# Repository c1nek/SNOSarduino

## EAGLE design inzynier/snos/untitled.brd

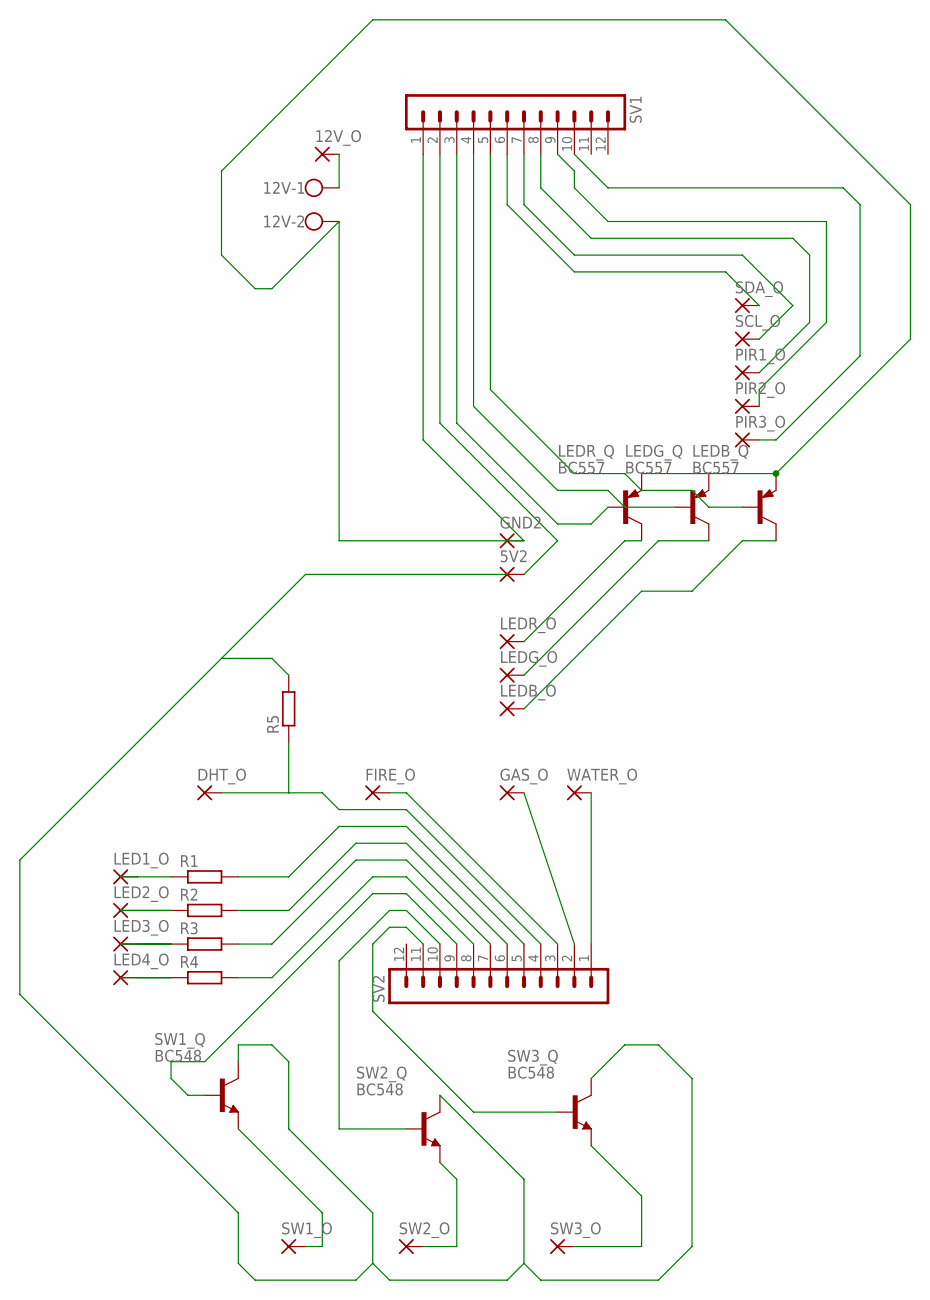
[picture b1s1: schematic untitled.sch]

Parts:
5V2, 12V_O: 1,6/0,8
12V: W237-102
DHT_O: 1,6/0,8
FIRE_O: 1,6/0,8
GAS_O: 1,6/0,8
GND2: 1,6/0,8
LED1_O, LED2_O, LED3_O, LED4_O: 1,6/0,8
LEDB_O: 1,6/0,8
LEDB_Q: BC557; TO92-EBC
LEDG_O: 1,6/0,8
LEDG_Q: BC557; TO92-EBC
LEDR_O: 1,6/0,8
LEDR_Q: BC557; TO92-EBC
PIR1_O, PIR2_O, PIR3_O: 1,6/0,8
R1, R2, R3, R4, R5: R-EU_0207/15; 0207/15
SCL_O: 1,6/0,8
SDA_O: 1,6/0,8
SV1, SV2: MA12-1W
SW1_O, SW2_O, SW3_O: 1,6/0,8
SW1_Q, SW2_Q, SW3_Q: BC548; TO92-EBC
WATER_O: 1,6/0,8

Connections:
unnamed: 12V.2, GND2.1, LEDB_Q.E, LEDG_Q.E, LEDR_Q.E, SV1.1
unnamed: 5V2.1, SV1.2
unnamed: LEDR_Q.B, SV1.3
unnamed: LEDG_Q.B, SV1.4
unnamed: LEDB_Q.B, SV1.5
unnamed: SDA_O.1, SV1.6
unnamed: SCL_O.1, SV1.7
unnamed: PIR1_O.1, SV1.8
unnamed: PIR2_O.1, SV1.9
unnamed: PIR3_O.1, SV1.10
unnamed: SV2.1, WATER_O.1
unnamed: GAS_O.1, SV2.2
unnamed: FIRE_O.1, SV2.3
unnamed: DHT_O.1, R5.1, SV2.4
unnamed: SV2.11, SW3_Q.B
unnamed: SV2.10, SW2_Q.B
unnamed: SV2.9, SW1_Q.B
unnamed: R4.2, SV2.8
unnamed: R3.2, SV2.7
unnamed: R2.2, SV2.6
unnamed: R1.2, SV2.5
unnamed: LED4_O.1, R4.1
unnamed: LED3_O.1, R3.1
unnamed: LED2_O.1, R2.1
unnamed: LED1_O.1, R1.1
unnamed: LEDR_O.1, LEDR_Q.C
unnamed: LEDG_O.1, LEDG_Q.C
unnamed: R5.2, SW1_Q.C, SW2_Q.C, SW3_Q.C
unnamed: LEDB_O.1, LEDB_Q.C
unnamed: SW1_O.1, SW1_Q.E
unnamed: SW2_O.1, SW2_Q.E
unnamed: SW3_O.1, SW3_Q.E
unnamed: 12V.1, 12V_O.1

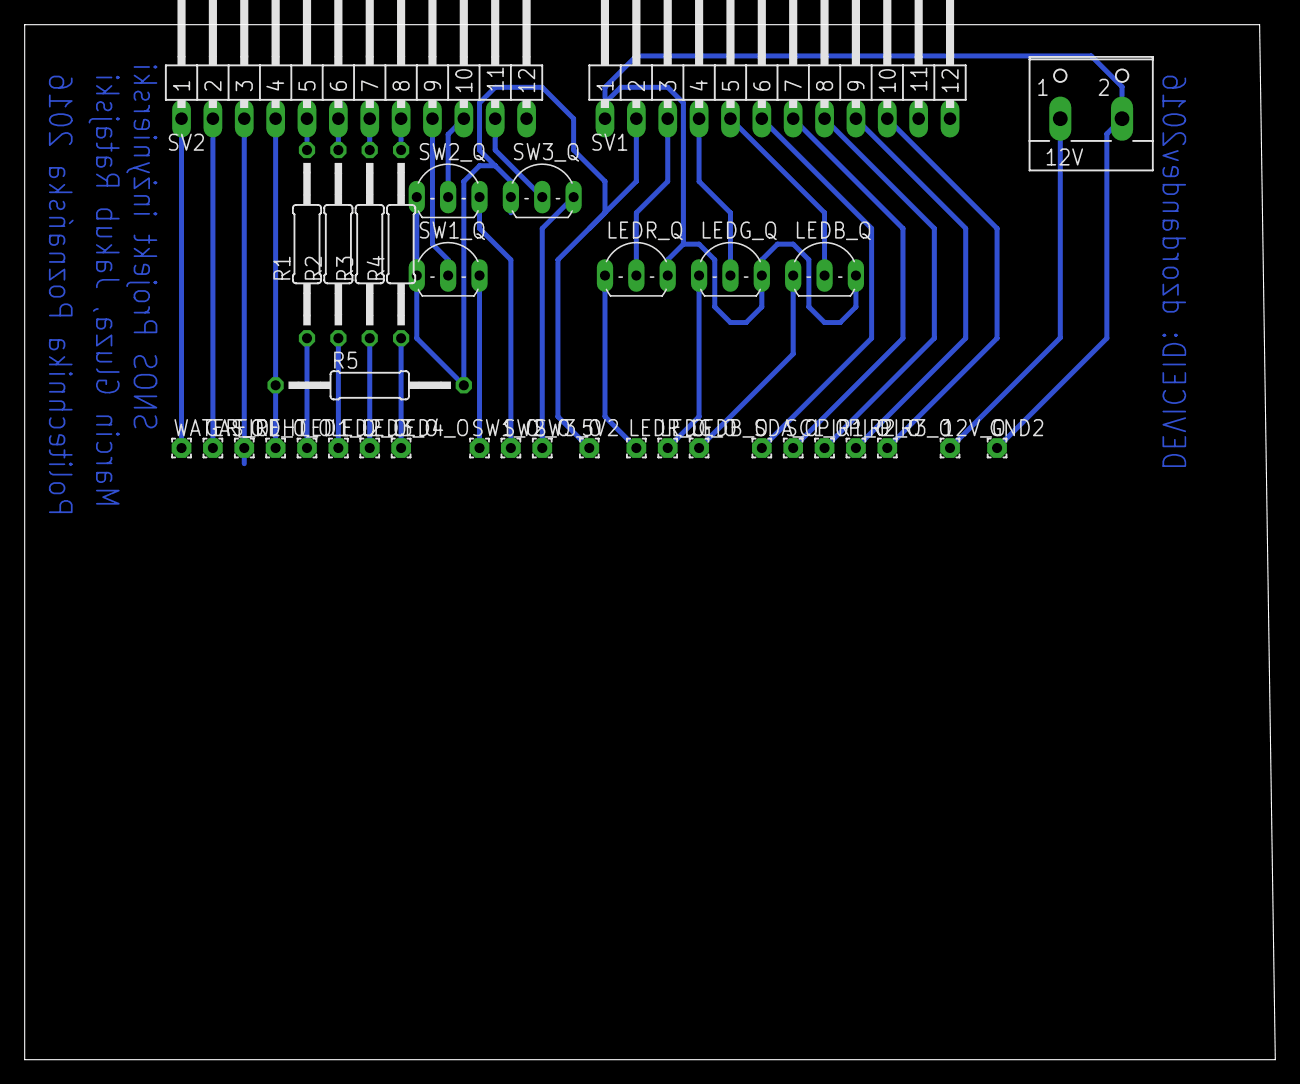
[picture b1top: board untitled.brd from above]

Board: 2 copper layers, 101.3 x 83.8 mm, 36 parts (0 on the bottom side), 33 nets.

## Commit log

2016-01-28 :boom::camel: Added .gitattributes & .gitignore files
2016-02-10 świeta wersja
2016-02-11 obsluga przelazcników
2016-02-11 jakies pierdy xD
2016-02-14 dodana obsluga paska RGB
2016-02-16 popraweczki
2016-02-16 added board project
2016-02-23 a few changes
